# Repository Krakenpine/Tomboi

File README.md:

# Tomboi
 Sample player with Daisy

 Very overengineered with effects and tonally playable multisampled sounds.
 Currently this repository includes only seven drum samples from free libraries, using raw multisamples from rompler-synth woud probably be a copyright violation, so I need to create my own for public examples.

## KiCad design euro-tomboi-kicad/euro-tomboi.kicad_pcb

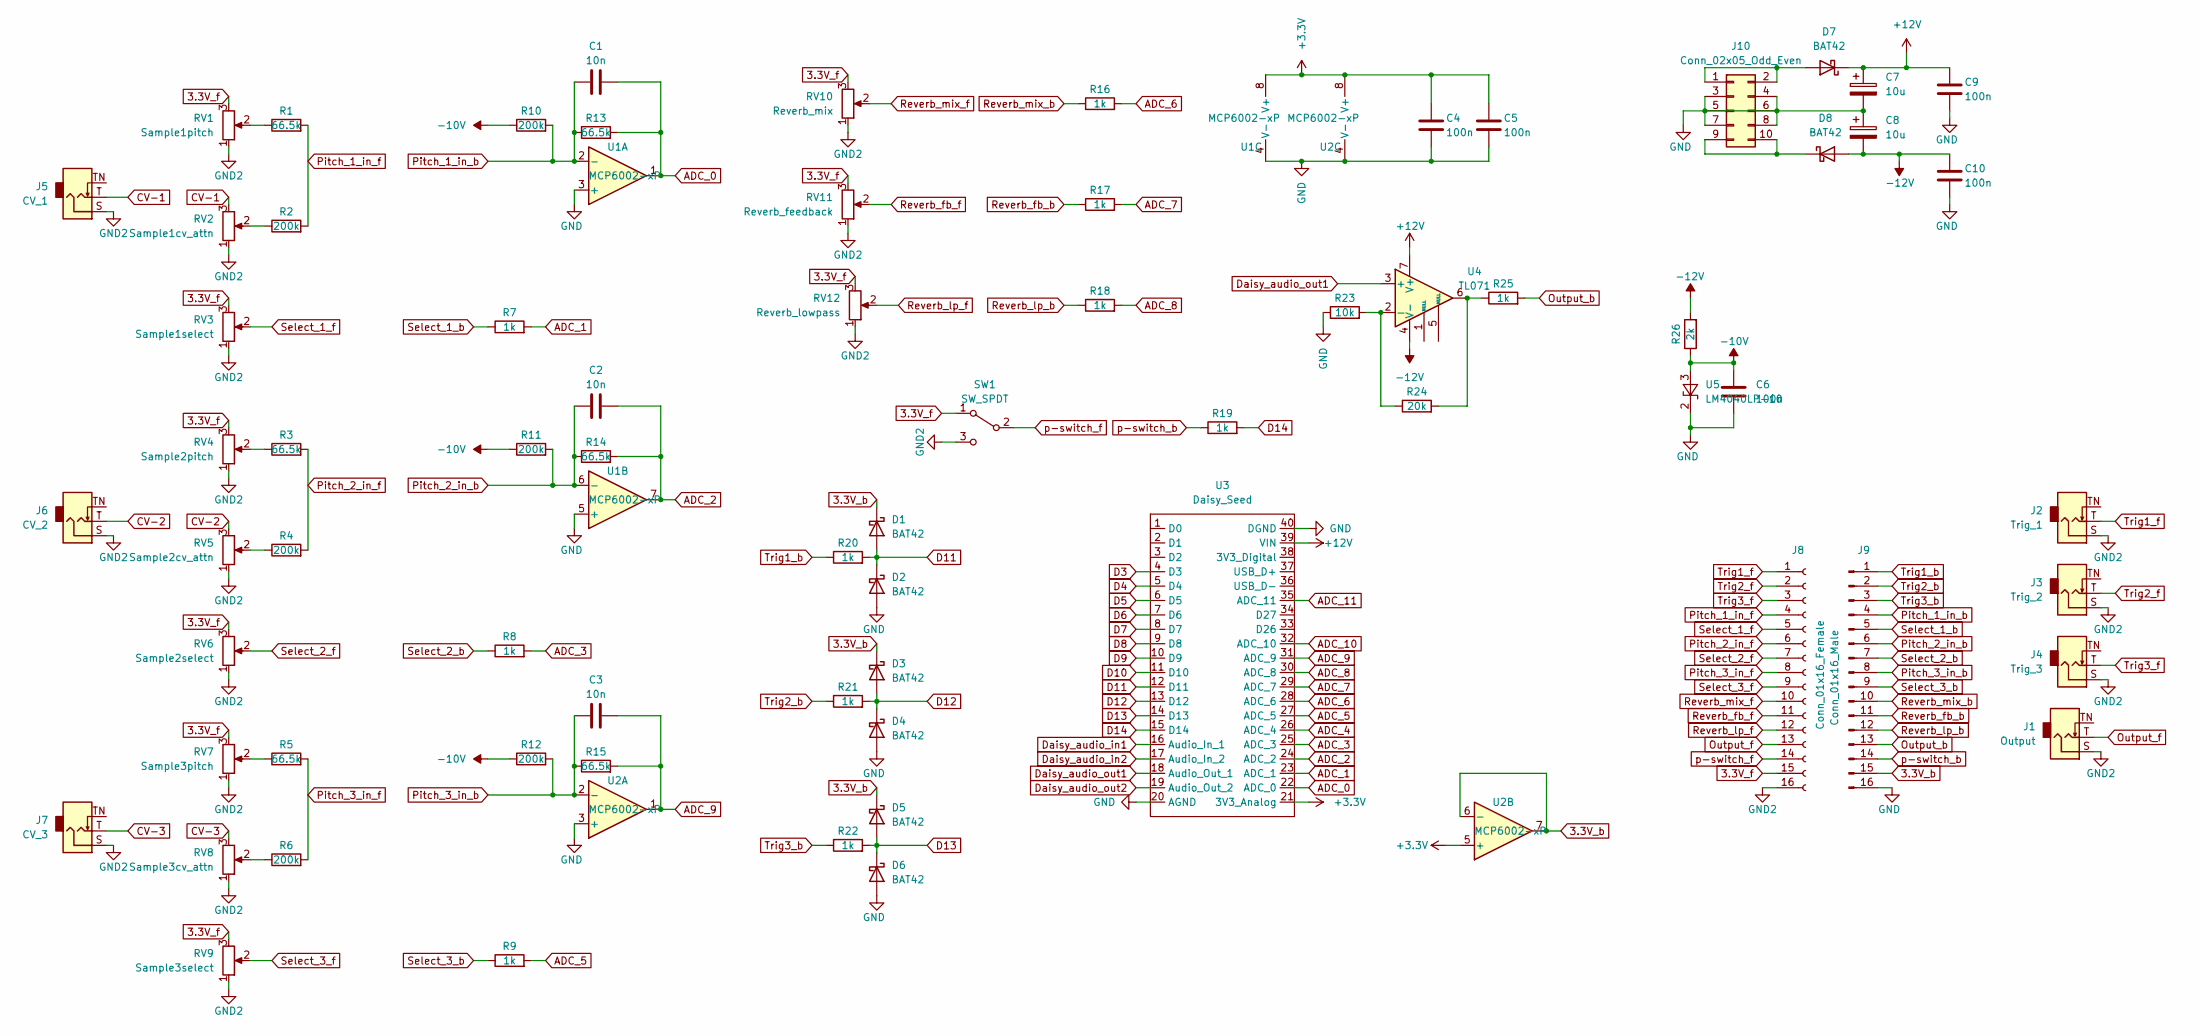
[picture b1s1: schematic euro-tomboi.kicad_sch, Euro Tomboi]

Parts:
C1, C2, C3: 10n; C_Disc_D5.0mm_W2.5mm_P5.00mm
C4, C5, C6, C9, C10: 100n; C_Disc_D5.0mm_W2.5mm_P5.00mm
C7, C8: 10u; CP_Radial_D5.0mm_P2.50mm
D1, D2, D3, D4, D5, D6, D7, D8: BAT42; D_DO-35_SOD27_P7.62mm_Horizontal
J1: Output; Jack_3.5mm_QingPu_WQP-PJ398SM_Vertical_CircularHoles_mid
J2: Trig_1; Jack_3.5mm_QingPu_WQP-PJ398SM_Vertical_CircularHoles_mid
J3: Trig_2; Jack_3.5mm_QingPu_WQP-PJ398SM_Vertical_CircularHoles_mid
J4: Trig_3; Jack_3.5mm_QingPu_WQP-PJ398SM_Vertical_CircularHoles_mid
J5: CV_1; Jack_3.5mm_QingPu_WQP-PJ398SM_Vertical_CircularHoles_mid
J6: CV_2; Jack_3.5mm_QingPu_WQP-PJ398SM_Vertical_CircularHoles_mid
J7: CV_3; Jack_3.5mm_QingPu_WQP-PJ398SM_Vertical_CircularHoles_mid
J8: Conn_01x16_Female; PinSocket_1x16_P2.54mm_Vertical
J9: Conn_01x16_Male; PinHeader_1x16_P2.54mm_Vertical
J10: Conn_02x05_Odd_Even; PinHeader_2x05_P2.54mm_Vertical
R1, R3, R5, R13, R14, R15: 66.5k; Omaresistor2
R2, R4, R6, R10, R11, R12: 200k; Omaresistor2
R7, R8, R9, R16, R17, R18, R19, R20, R21, R22, R25: 1k; Omaresistor2
R23: 10k; Omaresistor2
R24: 20k; Omaresistor2
R26: 2k; Omaresistor2
RV1: Sample1pitch; Potentiometer_Alpha_RD901F-40-00D_Single_Vertical_CircularH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
RV2: Sample1cv_attn; Potentiometer_Alpha_RD901F-40-00D_Single_Vertical_CircularH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
RV3: Sample1select; Potentiometer_Alpha_RD901F-40-00D_Single_Vertical_CircularH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
RV4: Sample2pitch; Potentiometer_Alpha_RD901F-40-00D_Single_Vertical_CircularH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
RV5: Sample2cv_attn; Potentiometer_Alpha_RD901F-40-00D_Single_Vertical_CircularH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
RV6: Sample2select; Potentiometer_Alpha_RD901F-40-00D_Single_Vertical_CircularH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
RV7: Sample3pitch; Potentiometer_Alpha_RD901F-40-00D_Single_Vertical_CircularH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
RV8: Sample3cv_attn; Potentiometer_Alpha_RD901F-40-00D_Single_Vertical_CircularH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
RV9: Sample3select; Potentiometer_Alpha_RD901F-40-00D_Single_Vertical_CircularH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
RV10: Reverb_mix; Potentiometer_Alpha_RD901F-40-00D_Single_Vertical_CircularH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
RV11: Reverb_feedback; Potentiometer_Alpha_RD901F-40-00D_Single_Vertical_CircularH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
RV12: Reverb_lowpass; Potentiometer_Alpha_RD901F-40-00D_Single_Vertical_CircularH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
SW1: SW_SPDT; submini switch
U1, U2: MCP6002-xP; DIP-8_W7.62mm
U3: Daisy_Seed; Daisy Seed
U4: TL071; DIP-8_W7.62mm
U5: LM4040LP-10; TO-92_Inline_Wide

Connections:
3.3V_b: D1.1 (K), D3.1 (K), D5.1 (K), J9.15, U2.6 (-), U2.7
3.3V_f: J8.15, RV1.3, RV3.3, RV4.3, RV6.3, RV7.3, RV9.3, RV10.3, RV11.3, RV12.3, SW1.1 (A)
+3V3: C4.1, C5.1, U1.8 (V+), U2.5 (+), U2.8 (V+), U3.21 (3V3_Analog)
+12V: C7.1, C9.1, D7.1 (K), U3.39 (VIN), U4.7 (V+)
-10V: C6.1, R10.1, R11.1, R12.1, R26.1, U5.3 (A)
-12V: C8.2, C10.1, D8.2 (A), R26.2, U4.4 (V-)
ADC_0: C1.2, R13.2, U1.1, U3.22 (ADC_0)
ADC_1: R7.2, U3.23 (ADC_1)
ADC_2: C2.2, R14.2, U1.7, U3.24 (ADC_2)
ADC_3: R8.2, U3.25 (ADC_3)
ADC_4: U3.26 (ADC_4)
ADC_5: R9.2, U3.27 (ADC_5)
ADC_6: R16.2, U3.28 (ADC_6)
ADC_7: R17.2, U3.29 (ADC_7)
ADC_8: R18.2, U3.30 (ADC_8)
ADC_9: C3.2, R15.2, U2.1, U3.31 (ADC_9)
ADC_10: U3.32 (ADC_10)
ADC_11: U3.35 (ADC_11)
CV-1: J5.T, RV2.3
CV-2: J6.T, RV5.3
CV-3: J7.T, RV8.3
D3: U3.4 (D3)
D4: U3.5 (D4)
D5: U3.6 (D5)
D6: U3.7 (D6)
D7: U3.8 (D7)
D8: U3.9 (D8)
D9: U3.10 (D9)
D10: U3.11 (D10)
D11: D1.2 (A), D2.1 (K), R20.2, U3.12 (D11)
D12: D3.2 (A), D4.1 (K), R21.2, U3.13 (D12)
D13: D5.2 (A), D6.1 (K), R22.2, U3.14 (D13)
D14: R19.2, U3.15 (D14)
Daisy_audio_in1: U3.16 (Audio_In_1)
Daisy_audio_in2: U3.17 (Audio_In_2)
Daisy_audio_out1: U3.18 (Audio_Out_1), U4.3 (+)
Daisy_audio_out2: U3.19 (Audio_Out_2)
GND: C4.2, C5.2, C6.2, C7.2, C8.1, C9.2, C10.2, D2.2 (A), D4.2 (A), D6.2 (A), J9.16, J10.3, J10.4, J10.5, J10.6, J10.7, J10.8, R23.1, U1.3 (+), U1.4 (V-), U1.5 (+), U2.3 (+), U2.4 (V-), U3.20 (AGND), U3.40 (DGND), U5.2 (K)
GND2: J1.S, J2.S, J3.S, J4.S, J5.S, J6.S, J7.S, J8.16, RV1.1, RV2.1, RV3.1, RV4.1, RV5.1, RV6.1, RV7.1, RV8.1, RV9.1, RV10.1, RV11.1, RV12.1, SW1.3 (C)
unnamed: D7.2 (A), J10.1, J10.2
unnamed: D8.1 (K), J10.9, J10.10
unnamed: R1.1, RV1.2
unnamed: R2.1, RV2.2
unnamed: R3.1, RV4.2
unnamed: R4.1, RV5.2
unnamed: R5.1, RV7.2
unnamed: R6.1, RV8.2
unnamed: R23.2, R24.1, U4.2 (-)
unnamed: R24.2, R25.1, U4.6
Output_b: J9.13, R25.2
Output_f: J1.T, J8.13
Pitch_1_in_b: C1.1, J9.4, R10.2, R13.1, U1.2 (-)
Pitch_1_in_f: J8.4, R1.2, R2.2
Pitch_2_in_b: C2.1, J9.6, R11.2, R14.1, U1.6 (-)
Pitch_2_in_f: J8.6, R3.2, R4.2
Pitch_3_in_b: C3.1, J9.8, R12.2, R15.1, U2.2 (-)
Pitch_3_in_f: J8.8, R5.2, R6.2
Reverb_fb_b: J9.11, R17.1
Reverb_fb_f: J8.11, RV11.2
Reverb_lp_b: J9.12, R18.1
Reverb_lp_f: J8.12, RV12.2
Reverb_mix_b: J9.10, R16.1
Reverb_mix_f: J8.10, RV10.2
Select_1_b: J9.5, R7.1
Select_1_f: J8.5, RV3.2
Select_2_b: J9.7, R8.1
Select_2_f: J8.7, RV6.2
Select_3_b: J9.9, R9.1
Select_3_f: J8.9, RV9.2
Trig1_b: J9.1, R20.1
Trig1_f: J2.T, J8.1
Trig2_b: J9.2, R21.1
Trig2_f: J3.T, J8.2
Trig3_b: J9.3, R22.1
Trig3_f: J4.T, J8.3
p-switch_b: J9.14, R19.1
p-switch_f: J8.14, SW1.2 (B)

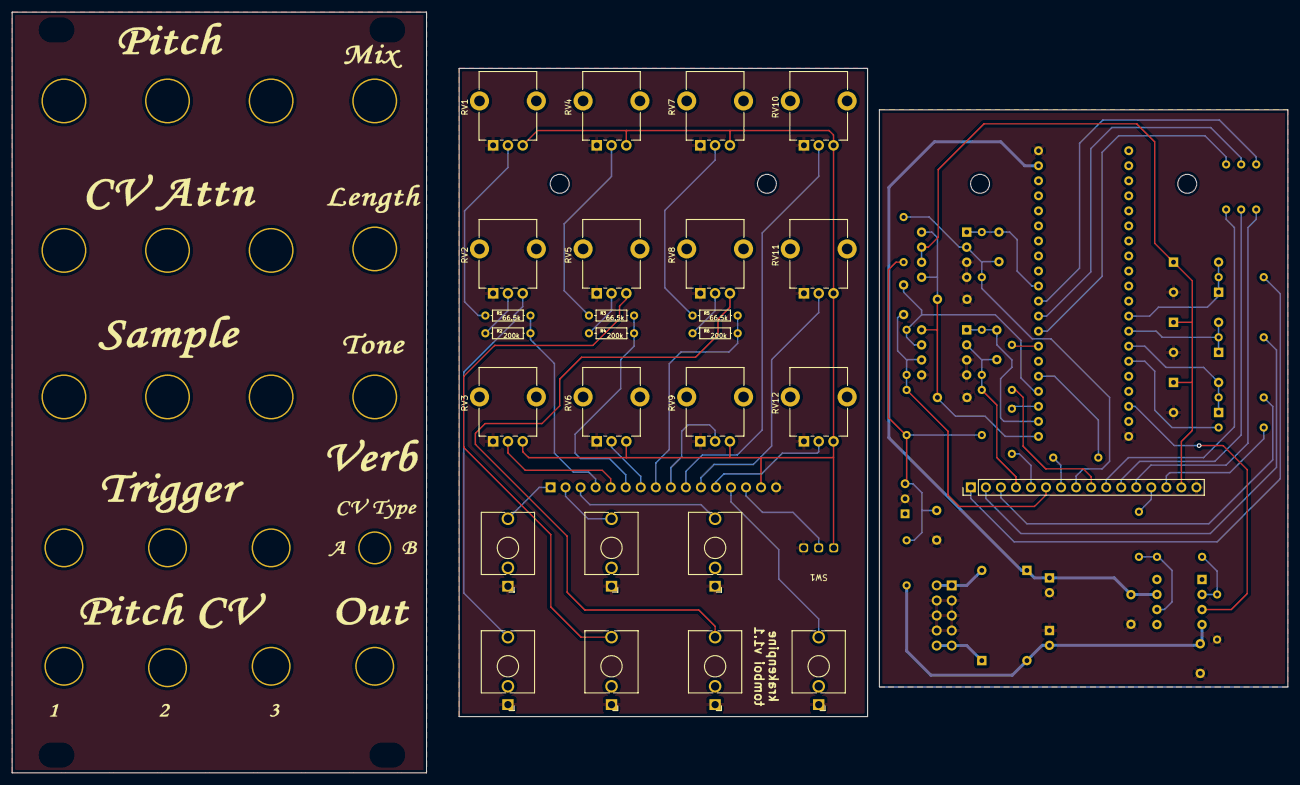
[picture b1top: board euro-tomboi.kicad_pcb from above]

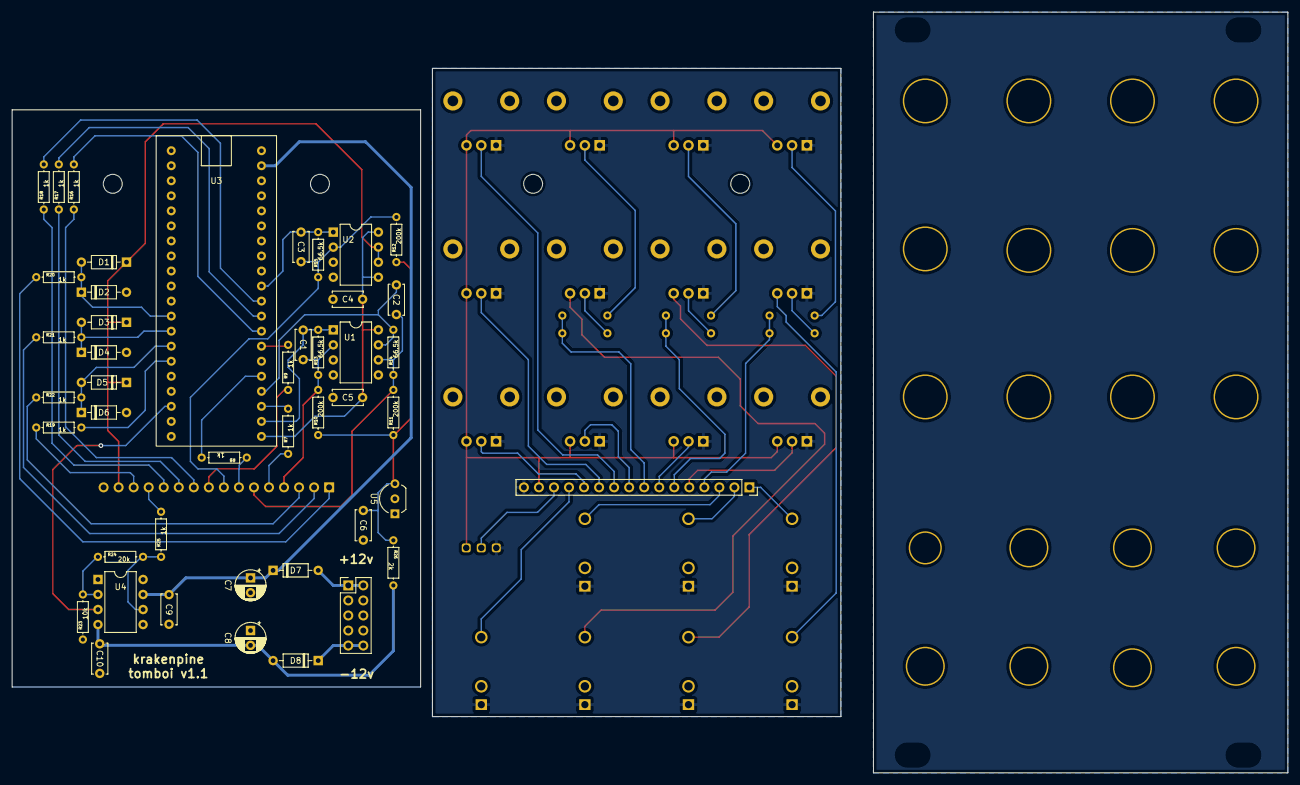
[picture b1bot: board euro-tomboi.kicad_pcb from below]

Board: 2 copper layers, 215.5 x 128.5 mm, 73 parts (45 on the bottom side), 63 nets.

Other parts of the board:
Ref**: Val**; euro-tomboi-kansi1

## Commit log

2023-10-02 First real commit
2023-10-03 Add missing sample.h
2023-10-03 Removing unnecessary variables
2023-10-03 fix pitch to midi note
2023-10-03 Remove old out-commented code
2023-10-03 Remove out-commented code from voice
2023-10-03 constexpr for samples
2023-10-03 Fix pitch knob when over 0.5
2023-11-14 cvToPitch & CV Type fixes
